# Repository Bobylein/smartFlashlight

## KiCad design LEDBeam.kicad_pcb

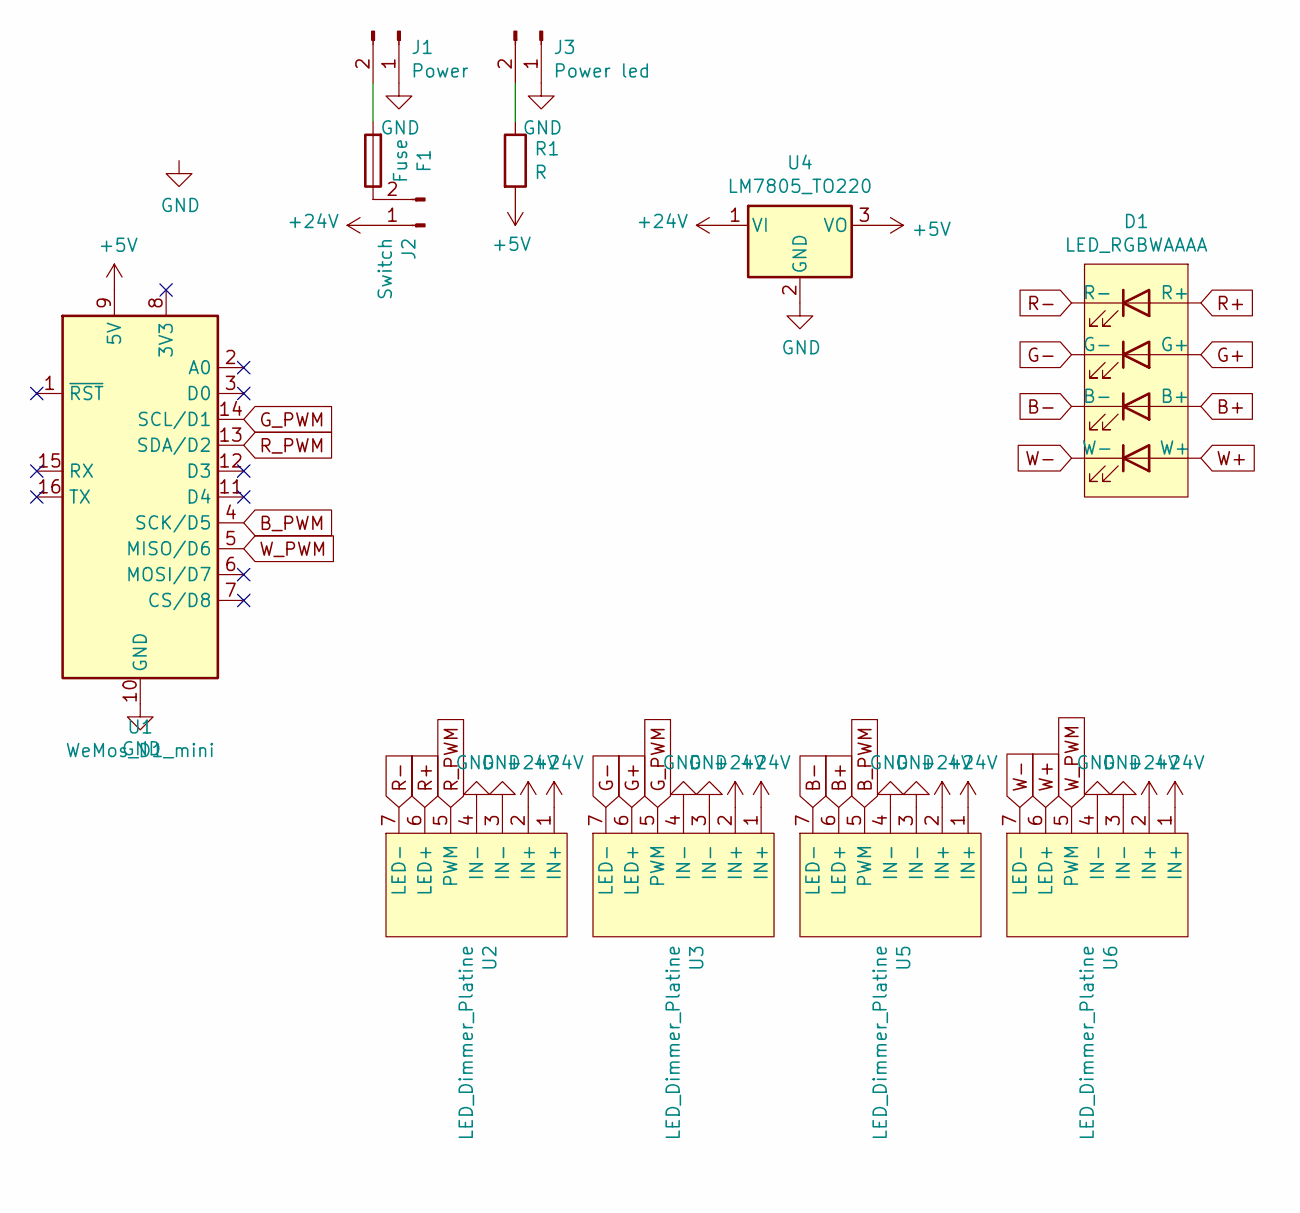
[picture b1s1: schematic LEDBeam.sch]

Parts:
D1: LED_RGBWAAAA; PinHeader_1x08_P2.54mm_Vertical
F1: Fuse; Fuseholder_Cylinder-5x20mm_Stelvio-Kontek_PTF78_Horizontal_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
J1: Power; SolderWire-0.5sqmm_1x02_P4.8mm_D0.9mm_OD2.3mm
J2: Switch; SolderWire-0.5sqmm_1x02_P4.8mm_D0.9mm_OD2.3mm
J3: Power led; SolderWire-0.5sqmm_1x02_P4.8mm_D0.9mm_OD2.3mm
R1: R; R_Axial_DIN0207_L6.3mm_D2.5mm_P10.16mm_Horizontal
U1: WeMos_D1_mini; WEMOS_D1_mini_light
U2, U3, U5, U6: LED_Dimmer_Platine; LED_Driver_module
U4: LM7805_TO220; TO-220-3_Vertical

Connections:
+5V: R1.2, U1.9 (5V), U4.3 (VO)
+24V: J2.1, U2.1 (IN+), U2.2 (IN+), U3.1 (IN+), U3.2 (IN+), U4.1 (VI), U5.1 (IN+), U5.2 (IN+), U6.1 (IN+), U6.2 (IN+)
B+: D1.5 (B+), U5.6 (LED+)
B-: D1.6 (B-), U5.7 (LED-)
B_PWM: U1.4 (SCK/D5), U5.5 (PWM)
G+: D1.3 (G+), U3.6 (LED+)
G-: D1.4 (G-), U3.7 (LED-)
GND: J1.1, J3.1, U1.10 (GND), U2.3 (IN-), U2.4 (IN-), U3.3 (IN-), U3.4 (IN-), U4.2 (GND), U5.3 (IN-), U5.4 (IN-), U6.3 (IN-), U6.4 (IN-)
G_PWM: U1.14 (SCL/D1), U3.5 (PWM)
unnamed: F1.1, J2.2
unnamed: F1.2, J1.2
unnamed: J3.2, R1.1
R+: D1.1 (R+), U2.6 (LED+)
R-: D1.2 (R-), U2.7 (LED-)
R_PWM: U1.13 (SDA/D2), U2.5 (PWM)
W+: D1.7 (W+), U6.6 (LED+)
W-: D1.8 (W-), U6.7 (LED-)
W_PWM: U1.5 (MISO/D6), U6.5 (PWM)

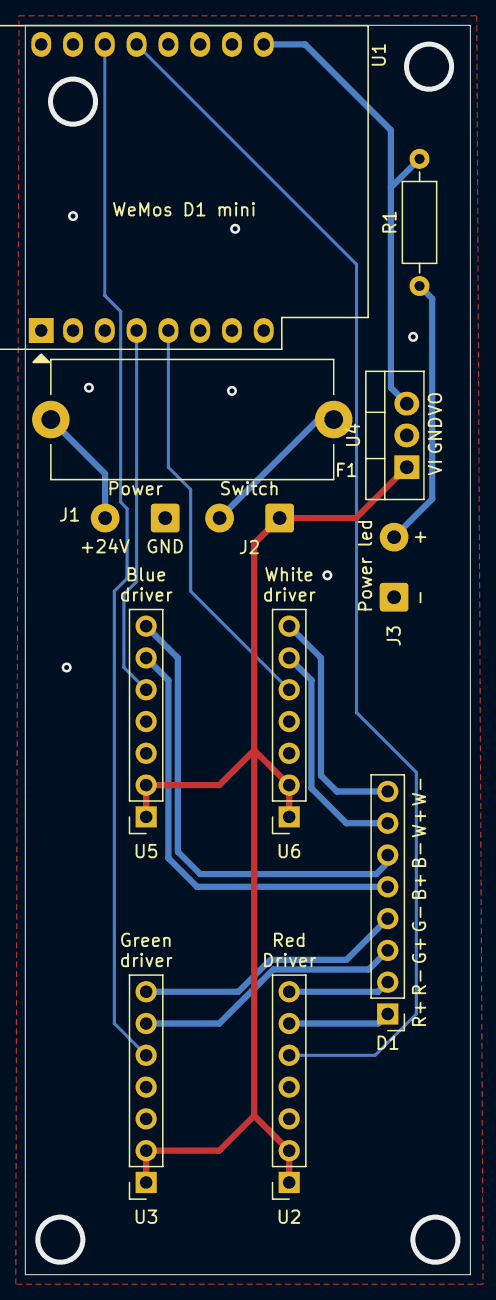
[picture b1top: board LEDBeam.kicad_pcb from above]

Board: 2 copper layers, 35.6 x 99.8 mm, 12 parts (0 on the bottom side), 18 nets.

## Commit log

2021-07-28 intial commit
2021-07-28 New board design
